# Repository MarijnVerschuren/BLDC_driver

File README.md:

# BLDC_driver
Brushless DC motor driver

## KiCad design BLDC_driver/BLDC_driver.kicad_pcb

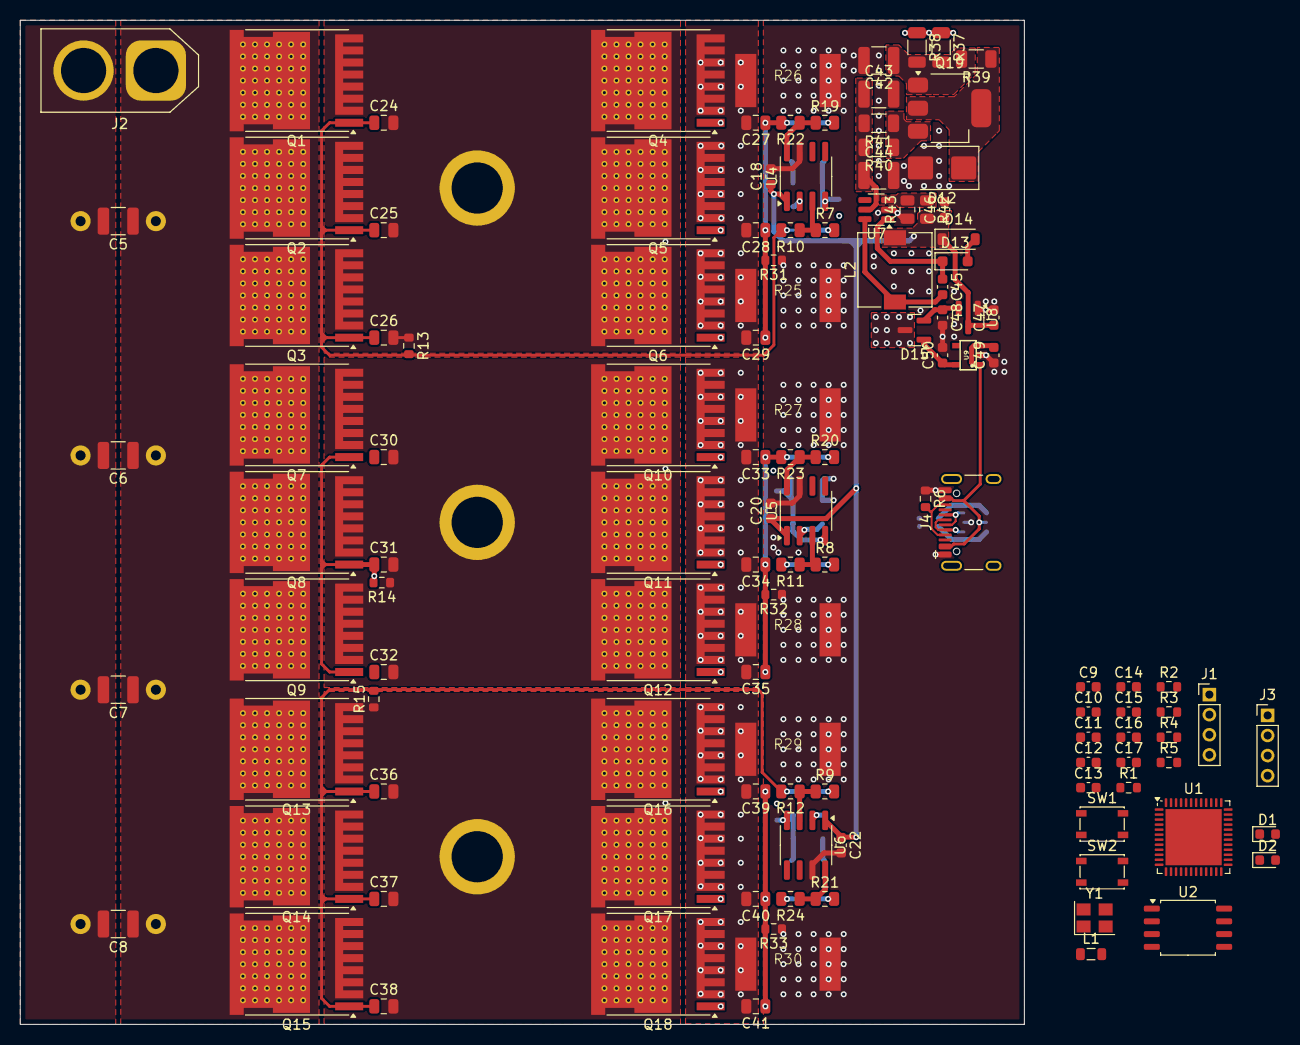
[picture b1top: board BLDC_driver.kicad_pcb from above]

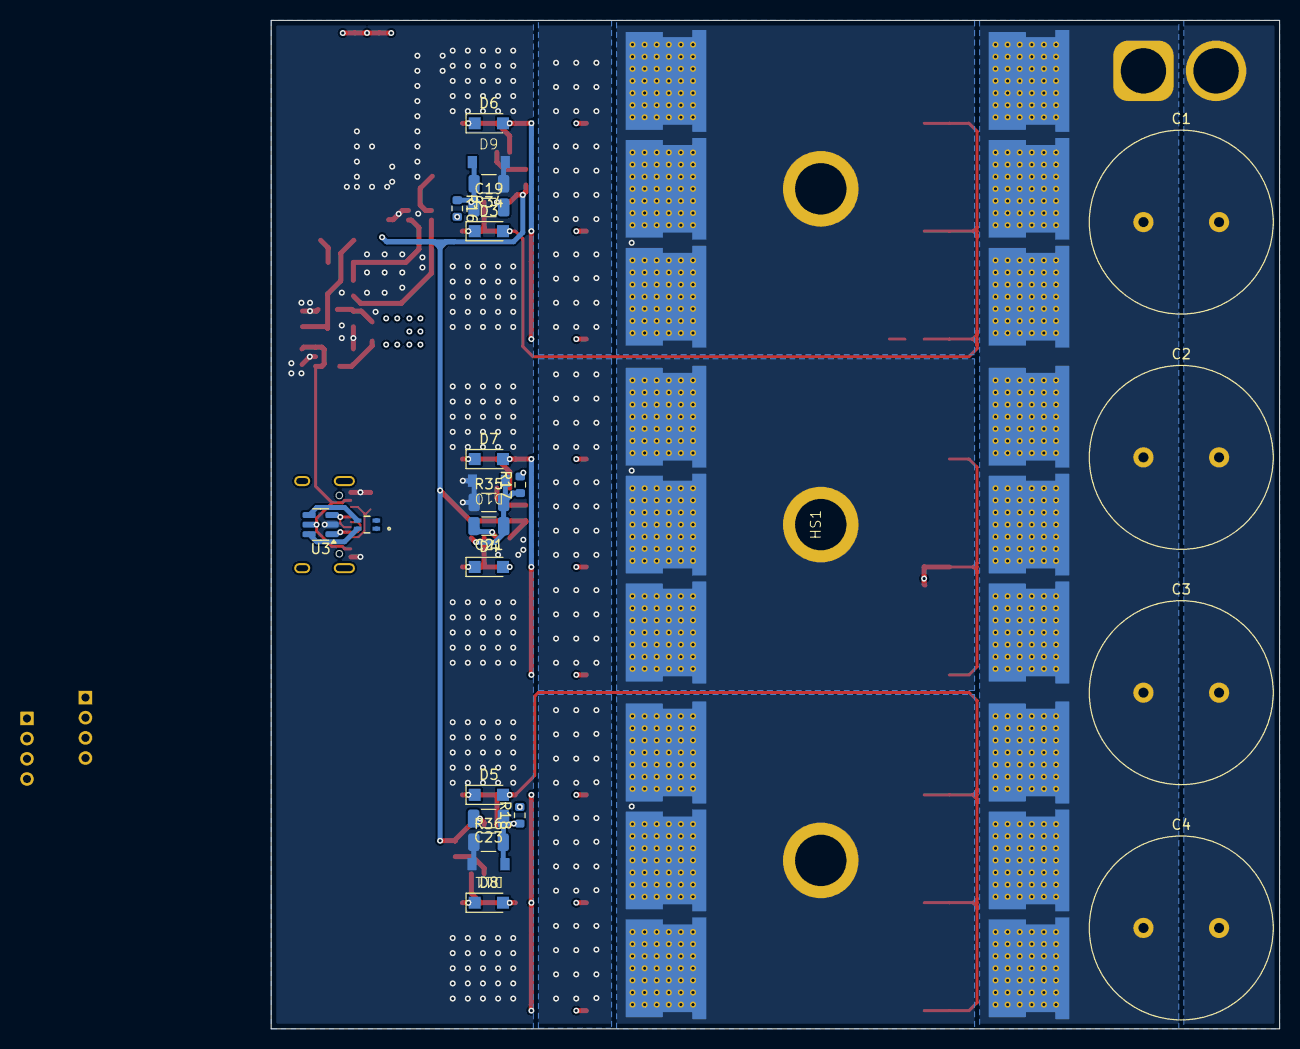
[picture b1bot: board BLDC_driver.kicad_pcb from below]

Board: 4 copper layers, 100.0 x 100.0 mm, 150 parts (25 on the bottom side), 58 nets.

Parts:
C1, C2, C3, C4: 820u/100v; C_Radial_D18.0mm_H35.5mm_P7.50mm
C5, C6, C7, C8, C42: 2u2/100v; C_1210_3225Metric
C9, C10, C11, C12, C14, C15, C18, C20, C22, C45: 100n; C_0603_1608Metric
C13, C48: 4u7; C_0603_1608Metric
C16, C17: 12p; C_0603_1608Metric
C19, C21, C23: 4u7/25V; C_1206_3216Metric
C24, C25, C26, C27, C28, C29, C30, C31, C32, C33, C34, C35, C36, C37, C38, C39, C40, C41: 3.3nF; C_0805_2012Metric
C43, C44: 4u7/100v; C_1210_3225Metric
C46: 22u; C_0603_1608Metric
C47, C49, C50: 1u; C_0603_1608Metric
D1: PWR; LED_0603_1608Metric
D2: STATUS; LED_0603_1608Metric
D3, D4, D5, D6, D7, D8: PMEG6010ER,115; Nexperia_CFP3_SOD-123W
D9, D10, D11: SL110PL; SOD-123FL
D12: BZG03C43-HM3-08; D_SMB
D13: 1N4148WS; D_SOD-323_HandSoldering
D14: MMSZ7V5T1G; D_SOD-123
D15: BAT54C; SOT-23
FL1: TDK ACM2012-900; ACM2012_900_2P_T002_Correct
HS1: SK_92/50_SA; SK_92-50_SA
J1: CTRL; PinHeader_1x04_P2.00mm_Vertical
J2: POWER; AMASS_XT60-F_1x02_P7.20mm_Vertical
J3: JTAG; PinHeader_1x04_P2.00mm_Vertical
J4: USB-C 16P; USB_C_Receptacle_HCTL_HC-TYPE-C-16P-01A
J5, J6, J7: 4mm_Banana_Jack_Vertical
L1: 10u; L_0805_2012Metric
L2: 56u; L_7.3x7.3_H4.5
Q1, Q2, Q3, Q4, Q5, Q6, Q7, Q8, Q9, Q10, Q11, Q12, Q13, Q14, Q15, Q16, Q17, Q18: AOTL66912; Infineon_PG-HSOF-8-1_ThermalVias
Q19: FZT853TA; SOT-223-3_TabPin2
R1, R6: 5k1; R_0603_1608Metric
R2: 1k; R_0603_1608Metric
R3, R5: 10k; R_0603_1608Metric
R4: 47; R_0603_1608Metric
R7, R8, R9, R10, R11, R12, R19, R20, R21, R22, R23, R24: 10R; R_0805_2012Metric
R13, R14, R15, R31, R32, R33: 47R; R_0603_1608Metric
R16, R17, R18: 2R2; R_0603_1608Metric
R25, R26, R27, R28, R29, R30: 500u; CSS2H-3920R-xxxx
R34, R35, R36: 33k; R_1206_3216Metric
R37, R38, R40, R41: 3r3; R_1206_3216Metric
R39: 2k2; R_1206_3216Metric
R42: 140k; R_0805_2012Metric
R43: 10k; R_0805_2012Metric
SW1, SW2: BTN; SW_SPST_PTS810
U1: STM32F412CEUx; QFN-48-1EP_7x7mm_P0.5mm_EP5.6x5.6mm
U2: W25Q128JVS; SOIC-8_5.23x5.23mm_P1.27mm
U3: USBLC6-2SC6; SOT-23-6
U4, U5, U6: SOIC-8_3.9x4.9mm_P1.27mm
U7: MCP16331x-xCH; SOT-23-6
U8: MCP1754S-3302xCB; SOT-23
U9: AP7343; SOT-25
Y1: 25MHz; Crystal_SMD_3225-4Pin_3.2x2.5mm

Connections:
+3.3VA: C14.1, L1.2
+3V3: C9.1, C10.1, C11.1, C12.1, C13.1, D15.3, J3.1, L1.1, R1.1, R2.1, R3.1, SW1.2, U2.8 (VCC)
+5V: C49.2, J4.A4 (VBUS), J4.A9 (VBUS), J4.B4 (VBUS), J4.B9 (VBUS), U3.5 (VBUS), U9.1 (VIN), U9.3 (EN)
+12V: C18.1, C20.1, C22.1, C46.1, C47.1, D14.1 (K), L2.2, R42.2, U4.1 (VDD), U5.1 (VDD), U6.1 (VDD), U8.3 (VI)
+43V: C43.1, C44.1, R40.2, R41.2, U7.5 (V_{IN})
/BOOT0: R5.1, SW1.1
/HSE_IN: C16.1, Y1.1
/NRST: C15.2, R3.2, SW2.1
/USB/FL_N: FL1.1, U3.6 (I/O1)
/USB/FL_P: FL1.4, U3.4 (I/O2)
/inverter stage/A: C24.2, C25.2, C26.2, J5.1, Q1.2 (S), Q2.2 (S), Q3.2 (S), Q4.3 (D), Q5.3 (D), Q6.3 (D), R13.1, R16.2
/inverter stage/A_CSP: C27.2, C28.2, C29.2, Q4.2 (S), Q5.2 (S), Q6.2 (S), R25.1, R26.1
/inverter stage/B: C30.2, C31.2, C32.2, J6.1, Q7.2 (S), Q8.2 (S), Q9.2 (S), Q10.3 (D), Q11.3 (D), Q12.3 (D), R14.1, R17.2
/inverter stage/B_CSP: C33.2, C34.2, C35.2, Q10.2 (S), Q11.2 (S), Q12.2 (S), R27.1, R28.1
/inverter stage/C: C36.2, C37.2, C38.2, J7.1, Q13.2 (S), Q14.2 (S), Q15.2 (S), Q16.3 (D), Q17.3 (D), Q18.3 (D), R15.1, R18.2
/inverter stage/C_CSP: C39.2, C40.2, C41.2, Q16.2 (S), Q17.2 (S), Q18.2 (S), R29.1, R30.1
/inverter stage/HA: C24.1, C25.1, C26.1, D3.2 (A), Q1.1 (G), Q2.1 (G), Q3.1 (G), R10.2, R13.2
/inverter stage/HB: C30.1, C31.1, C32.1, D4.2 (A), Q7.1 (G), Q8.1 (G), Q9.1 (G), R11.2, R14.2
/inverter stage/HC: C36.1, C37.1, C38.1, D5.2 (A), Q13.1 (G), Q14.1 (G), Q15.1 (G), R12.2, R15.2
/inverter stage/HSA: R7.1, R10.1, U4.3 (HO)
/inverter stage/HSB: R8.1, R11.1, U5.3 (HO)
/inverter stage/HSC: R9.1, R12.1, U6.3 (HO)
/inverter stage/LA: C27.1, C28.1, C29.1, D6.2 (A), Q4.1 (G), Q5.1 (G), Q6.1 (G), R22.2, R31.2
/inverter stage/LB: C33.1, C34.1, C35.1, D7.2 (A), Q10.1 (G), Q11.1 (G), Q12.1 (G), R23.2, R32.2
/inverter stage/LC: C39.1, C40.1, C41.1, D8.2 (A), Q16.1 (G), Q17.1 (G), Q18.1 (G), R24.2, R33.2
/inverter stage/LSA: R19.1, R22.1, U4.8 (LO)
/inverter stage/LSB: R20.1, R23.1, U5.8 (LO)
/inverter stage/LSC: R21.1, R24.1, U6.8 (LO)
/inverter stage/PHA: C19.1, D9.1 (K), R16.1, R34.2, U4.4 (HS)
/inverter stage/PHB: C21.1, D10.1 (K), R17.1, R35.2, U5.4 (HS)
/inverter stage/PHC: C23.1, D11.1 (K), R18.1, R36.2, U6.4 (HS)
GND: C1.2, C2.2, C3.2, C4.2, C5.2, C6.2, C7.2, C8.2, C9.2, C10.2, C11.2, C12.2, C13.2, C14.2, C15.1, C16.2, C17.2, C18.2, C20.2, C22.2, C42.2, C43.2, C44.2, C46.2, C47.2, C48.2, C49.1, C50.2, D1.1 (K), D9.2 (A), D10.2 (A), D11.2 (A), D12.2 (A), J2.2, J3.4, J4.A1 (GND), J4.A12 (GND), J4.B1 (GND), J4.B12 (GND), R5.2, R6.1, R25.2, R26.2, R27.2, R28.2, R29.2, R30.2, R31.1, R32.1, R33.1, R34.1, R35.1, R36.1, R43.1, SW2.2, U2.4 (GND), U3.2 (GND), U4.7 (VSS), U5.7 (VSS), U6.7 (VSS), U7.2 (GND), U8.1 (GND), U9.2 (GND), Y1.2, Y1.4
unnamed: C17.1, R4.2, Y1.3
unnamed: D1.2 (A), R1.2
unnamed: D2.2 (A), R2.2
unnamed: D3.1 (K), R7.2
unnamed: D4.1 (K), R8.2
unnamed: D5.1 (K), R9.2
unnamed: D6.1 (K), R19.2
unnamed: D7.1 (K), R20.2
unnamed: D8.1 (K), R21.2
unnamed: D12.1 (K), Q19.2 (B), R39.1
unnamed: D13.2 (A), D14.2 (A)
unnamed: C45.1, D13.1 (K), U7.1 (BOOST)
unnamed: J4.A5 (CC1), J4.B5 (CC2), R6.2
unnamed: J4.A6 (D+), J4.B6 (D+), U3.3 (I/O2)
unnamed: J4.A7 (D-), J4.B7 (D-), U3.1 (I/O1)
unnamed: C42.1, Q19.1 (C), R37.2, R38.2, R39.2
unnamed: Q19.3 (E), R40.1, R41.1
unnamed: U1.23 (VSS), U1.35 (VSS), U1.47 (VSS), U1.49 (VSS)
unnamed: C19.2, U4.2 (HB)
unnamed: C21.2, U5.2 (HB)
unnamed: C23.2, U6.2 (HB)
unnamed: C45.2, L2.1, U7.6 (SW)
unnamed: R42.1, R43.2, U7.3 (V_{FB})
unnamed: C48.1, D15.2, U8.2 (VO)
unnamed: C50.1, D15.1, U9.5 (VOUT)
VPWR: C1.1, C2.1, C3.1, C4.1, C5.1, C6.1, C7.1, C8.1, J2.1, Q1.3 (D), Q2.3 (D), Q3.3 (D), Q7.3 (D), Q8.3 (D), Q9.3 (D), Q13.3 (D), Q14.3 (D), Q15.3 (D), R37.1, R38.1

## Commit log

2024-08-09 Created project
2024-08-13 Layout progress
2024-08-18 Rough inverter stage layout
2024-08-21 New design
2024-08-27 Started on power conversion section
2024-08-28 Power converter layout
